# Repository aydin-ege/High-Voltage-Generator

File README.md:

# High-Voltage-Generator
An improved ZVS circuit on PCB with a safety oriented design that generates 400V from low voltage DC for the purposes of operating a Geiger-Müller Tube

Check EEE313 Course Project Report.pdf and PHYS212_Final_Report.pdf for more info.

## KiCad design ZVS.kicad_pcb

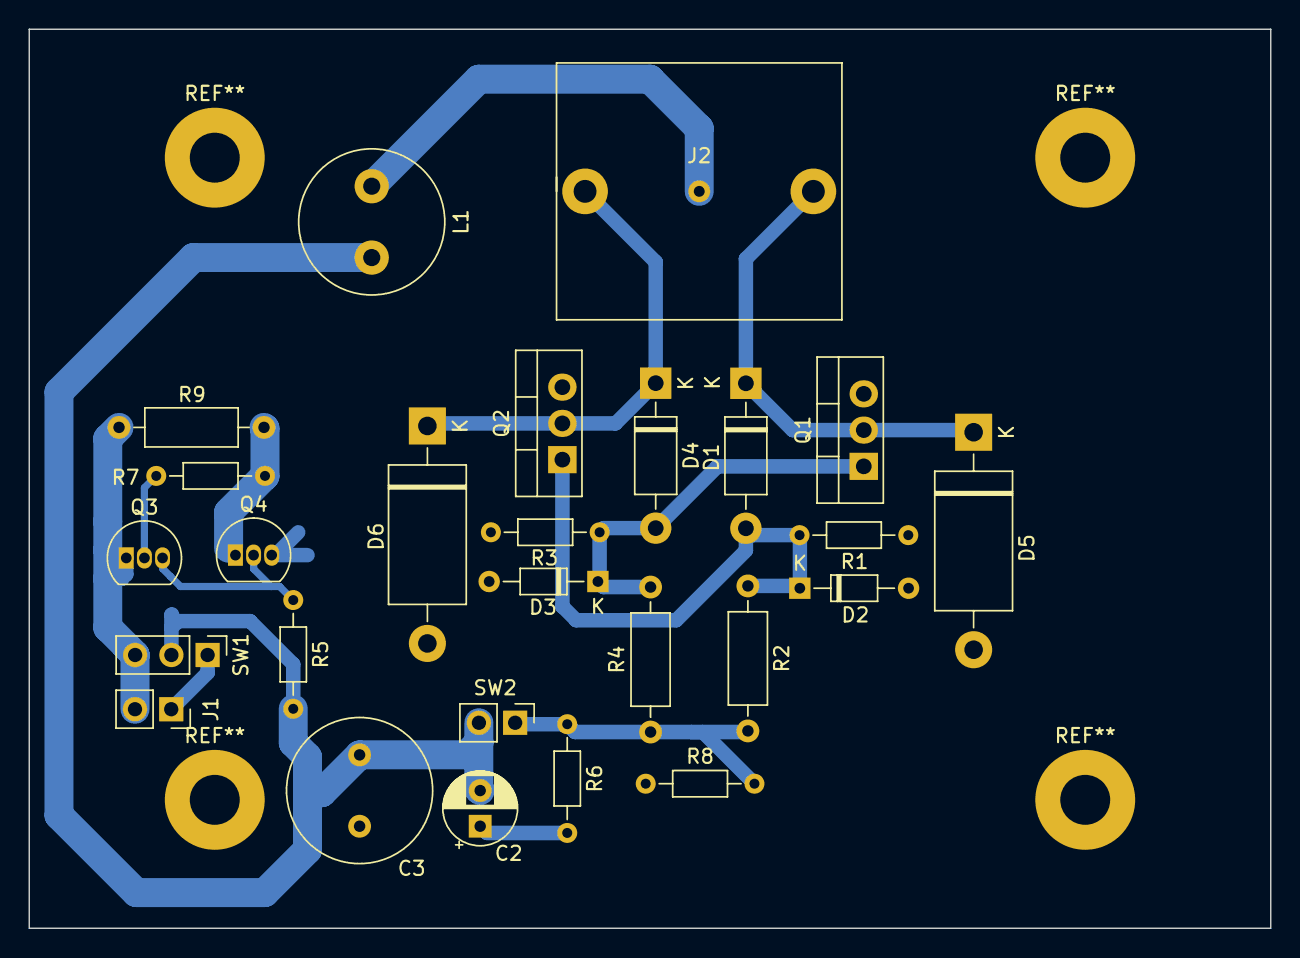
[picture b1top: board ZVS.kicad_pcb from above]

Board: 2 copper layers, 87.0 x 63.0 mm, 26 parts (0 on the bottom side), 14 nets.

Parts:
C2: 1u; CP_Radial_D5.0mm_P2.50mm
C3: 1000u; C_Radial_D10.0mm_H16.0mm_P5.00mm
D1, D4: 1N5819; D_DO-41_SOD81_P10.16mm_Horizontal
D2, D3: 3V9; D_DO-34_SOD68_P7.62mm_Horizontal
D5, D6: 1N53xxB; D_DO-201_P15.24mm_Horizontal
J1: Conn_01x02; PinSocket_1x02_P2.54mm_Vertical
J2: Conn_01x03; Transformer_HV
L1: 47u; L_Radial_D10.0mm_P5.00mm_Neosid_SD12k_style3
Q1, Q2: IRLZ44N; TO-220-3_Vertical
Q3, Q4: 2N3904; TO-92_Inline
R1, R3: 50k; R_Axial_DIN0204_L3.6mm_D1.6mm_P7.62mm_Horizontal
R2, R4: 56; R_Axial_DIN0207_L6.3mm_D2.5mm_P10.16mm_Horizontal
R5: 570; R_Axial_DIN0204_L3.6mm_D1.6mm_P7.62mm_Horizontal
R6: 10; R_Axial_DIN0204_L3.6mm_D1.6mm_P7.62mm_Horizontal
R7, R8: 1k; R_Axial_DIN0204_L3.6mm_D1.6mm_P7.62mm_Horizontal
R9: 0.1; R_Axial_DIN0207_L6.3mm_D2.5mm_P10.16mm_Horizontal
SW1: SW_SPDT; PinHeader_1x03_P2.54mm_Vertical
SW2: SW_Push; PinHeader_1x02_P2.54mm_Vertical

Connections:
+4V: C2.2, C3.1, L1.2, R5.2, SW1.2, SW2.2
-BATT: J1.2, Q3.1, R9.2, SW1.3
/CENTER_TAP: J2.2, L1.1
/ENABLE: R2.2, R4.1, R6.1, R8.2, SW2.1
/GATE_L: D3.1, D4.2, Q1.1, R3.2, R4.2
/GATE_R: D1.2, D2.1, Q2.1, R1.2, R2.1
/TANK_L: D1.1, D5.1, J2.3, Q1.2
/TANK_R: D4.1, D6.1, J2.1, Q2.2
GND: C3.2, D2.2, D3.2, D5.2, D6.2, Q1.3, Q2.3, Q4.3, R1.1, R3.1, R8.1
unnamed: C2.1, R6.2
unnamed: J1.1, SW1.1
unnamed: Q3.2, R7.1
unnamed: Q3.3, Q4.2, R5.1
unnamed: Q4.1, R7.2, R9.1

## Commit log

2021-10-26 Create LICENSE
